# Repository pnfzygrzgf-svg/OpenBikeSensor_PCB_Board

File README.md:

# OpenBikeSensor PCB

**Hinweis:** Dieses Repository ist ein Klon/Fork des offiziellen
[OpenBikeSensor PCB-Repositories](https://github.com/openbikesensor/OpenBikeSensor_PCB_Board) und enthält zusätzliche Erweiterungen.

**Neu in diesem Fork:**
- **OpenBikeSensor Lite LiDAR** (`OpenBikeSensorLiteLidar/`) — PCB-Variante mit 2x TF-Luna LiDAR statt Ultraschallsensoren

## Versionen

### OpenBikeSensor Lite LiDAR

Im Verzeichnis `OpenBikeSensorLiteLidar` findest du die Dateien für das Modell
OpenBikeSensor Lite LiDAR (2x TF-Luna). Diese Variante basiert auf dem Lite-Konzept
(Messelektronik + Kommunikation, Programmlogik überwiegend auf dem Handy), nutzt
aber LiDAR zur Abstandsmessung.

* [Gerber (ZIP)](./OpenBikeSensorLiteLidar/plot/OpenBikeSensorLiteLidar-gerbers.zip)
* [KiCad PCB](./OpenBikeSensorLiteLidar/OpenBikeSensorLiteLidar.kicad_pcb)

### OpenBikeSensor

Dies ist der Standard-OpenBikeSensor als eigenständiges Gerät, hergestellt aus
vielen fertig verfügbaren Modulen (ESP32 Devkit, GPS, SD-Karten-Modul,
Ultraschallsensor-Module, ...).

Die aktuelle Versionsnummer des OpenBikeSensor Clasic PCB ist `1.0.0`. Den veralteten Repositorystand der Vorversion findest du [hier](https://github.com/openbikesensor/OpenBikeSensor_PCB_Board/tree/00.03.12)

* [Gerber](OpenBikeSensor1.0.0-Gerber.zip)
* [Schaltplan, PDF](./OpenBikeSensor/generated/OpenBikeSensor-1.0.0-schematic.pdf)
* [Bestückungsplan, HTML](./OpenBikeSensor/generated/OpenBikeSensor-1.0.0-ibom.html)

### OpenBikeSensor Lite

Im Verzeichnis OpenBikeSensorLite findest du die Dateien für das Modell
OpenBikeSensor Lite. Dieser OpenBikeSensor hat nur Messelektronik,
Datenspeicher, Kommunikation und ein Großteil der Programmlogik läuft
auf dem Handy in der SimRa App.

### OpenBikeSensor Pro

Diese Variante des OpenBikeSensor ist ein vollständiger Nachbau aller
relevanter Teile der vorher als Modul gelieferten Funktionen in einer eigenen
Schaltung, und ist komplett maschinenbestückt bestellbar. Dies macht das Gerät
teurer und komplizierter herstellen zu lassen, aber es ist ein wesentlich
geringerer Eigenaufwand zur Fertigstellung ohne Löten elektronischer Module
nötig. Dieses Projekt is zur Zeit in der Entwicklung und hoffentlich im Laufe
des Jahres 2023 benutzbar.

## Bestellung bei Platinenherstellern

Ein Export der Projektdateien als "Gerber-Files" liegt im jeweiligen
Projektordner vor. Die meisten Hersteller von Platinen bieten einen
Online-Konfigurator an, in den diese Dateien hochgeladen werden können, und
welcher dann auch eine Vorschau bietet. In der Regel sollten diese Exports für
alle Hersteller funktionieren, die Anforderungen an die Genauigkeit der
Produktion sind relativ gering.

Die Standardeinstellungen für die Platine sind in der Regel vollkommen
ausreichend, das ist üblicherweise ein 2-Layer Board mit einfachem Surface
Finish (HASL) in 1.6mm Stärke (FR-4) und 1oz Kupferstärke. Bessere Optionen (z.
B. ENIG) sind möglich, aber nicht nötig. Die Einstellungen können nach Belieben
angepasst werden, insbesondere ästhetische Aspekte wie die Farbe der Boards.

Einige Hersteller (z. B. Aisler) können die KiCad-Dateien direkt importieren,
hier muss nur die `.kicad_pcb` Datei ausgewählt werden, diese enthält alle
Informationen des Designs.

Bei manchen Herstellern (z. B. JLCPCB) wird die Bestellnummer auf jedes Board
aufgedruckt, für einen kleinen Mehrbetrag kann dies vermieden werden. Gerade
bei größeren Bestellungen fällt diese Gebühr kaum ins Gewicht und ist sehr zu
empfehlen.

## Lizenz

Die eigenen Inhalte dieses Repositories sind lizensiert unter den Bedingungen
der GNU Lesser General Public License. Eine Kopie der Lizenz befindet sich in der
Datei `LICENSE` in diesem Verzeichnis.

Nicht unter diese Lizenz fallen:

* Die folgenden Dateien, welche leichte Modifikationen von Standard-Footprints
  der KiCad-Bibliothek sind und somit unter der entsprechende Lizenz
  ([CC-BY-SA 4.0 mit Modifikationen](https://www.kicad.org/libraries/license/))
  stehen:
    - `libs/OpenBikeSensor.pretty/CP_Radial_D4.0mm_P1.50mm.kicad_mod`
    - `libs/OpenBikeSensor.pretty/Connector_1x02.kicad_mod`
    - `libs/OpenBikeSensor.pretty/Connector_1x04.kicad_mod`
    - `libs/OpenBikeSensor.pretty/Connector_1x05_Display.kicad_mod`
    - `libs/OpenBikeSensor.pretty/Connector_1x06.kicad_mod`

## Update der Exportdateien

Die Dateien in `generated` können mit
[KiBot](https://github.com/INTI-CMNB/KiBot) automatisch aktualisiert werden.
Eine Konfigurationsdatei liegt im jeweiligen Projektverzeichnis vor. Ein
Ausführen von `kibot` im entsprechenden Unterverzeichnis (z. B. `cd
OpenBikeSensor`) erstellt alle Exportdateien neu. Bitte checke nur solche
Dateien in git ein, welche du in deinem Commit auch inhaltlich verändert hast
(z. B. den PDF Schaltplanexport wenn der Schaltplan verändert wurde, aber nicht
wenn nur das PCB Änderungen hat).

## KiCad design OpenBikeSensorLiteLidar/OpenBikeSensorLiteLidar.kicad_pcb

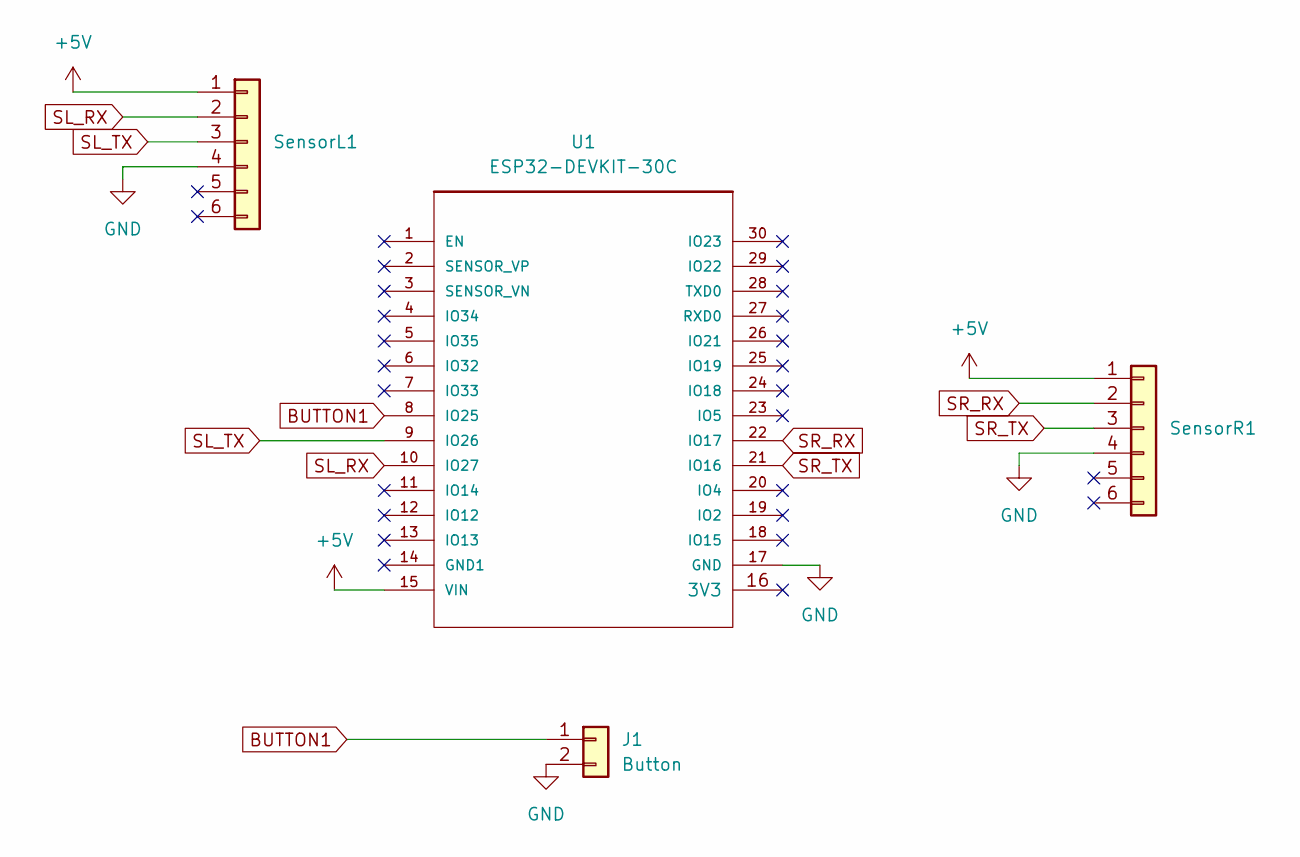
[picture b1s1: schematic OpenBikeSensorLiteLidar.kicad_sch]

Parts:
J1: Button; JST_EH_S2B-EH_1x02_P2.50mm_Horizontal
SensorL1: Conn_01x06; JST_XH_B6B-XH-A_1x06_P2.50mm_Vertical
SensorR1: Conn_01x06; JST_XH_B6B-XH-A_1x06_P2.50mm_Vertical
U1: ESP32-DEVKIT-30C; ESP32-WROOM-30-THT

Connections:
+5V: SensorL1.1, SensorR1.1, U1.15 (VIN)
BUTTON1: J1.1, U1.8 (IO25)
GND: J1.2, SensorL1.4, SensorR1.4, U1.17 (GND)
SL_RX: SensorL1.2, U1.10 (IO27)
SL_TX: SensorL1.3, U1.9 (IO26)
SR_RX: SensorR1.2, U1.22 (IO17)
SR_TX: SensorR1.3, U1.21 (IO16)

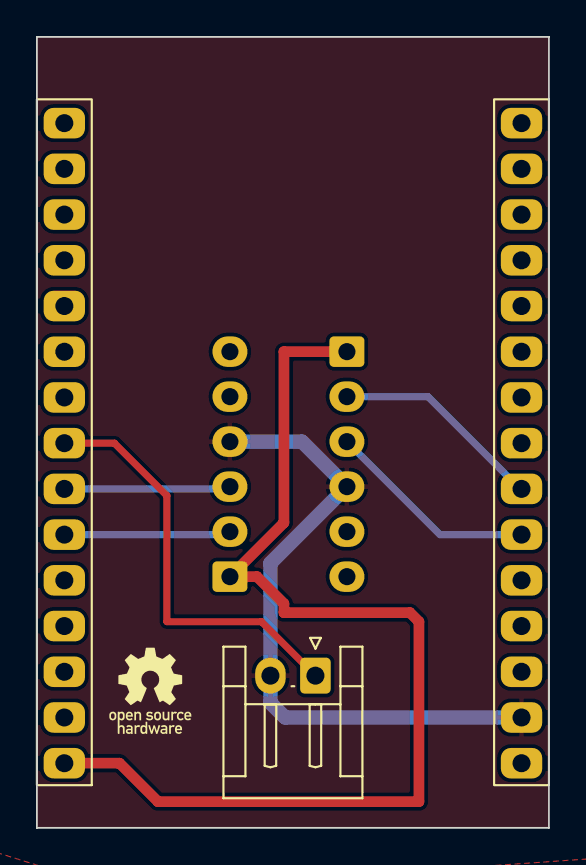
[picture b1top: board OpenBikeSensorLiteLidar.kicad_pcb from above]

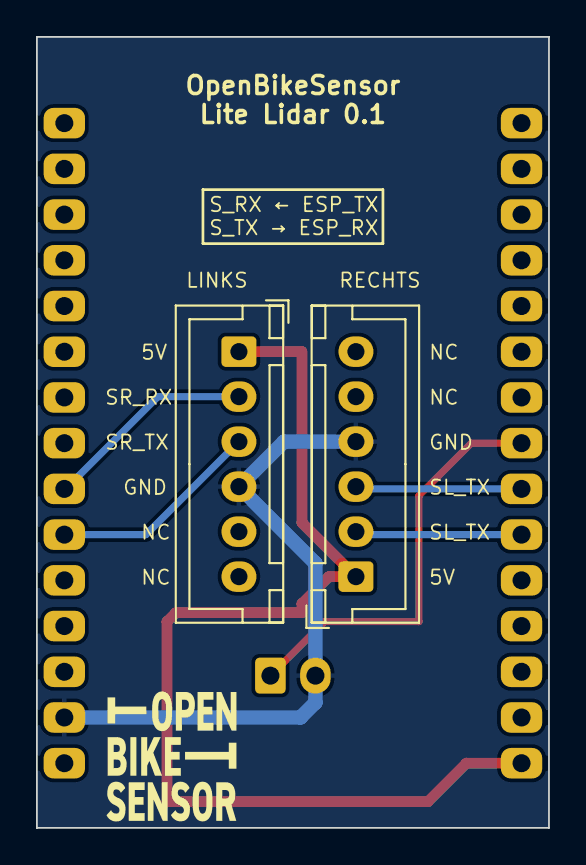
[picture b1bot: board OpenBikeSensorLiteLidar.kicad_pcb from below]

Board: 2 copper layers, 28.4 x 43.9 mm, 4 parts (2 on the bottom side), 7 nets.

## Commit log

2025-12-22 Add .gitignore for macOS files
2026-01-06 PCB für einen OpenBikeSensorLite mit Lidarsensoren
2026-01-06 Ignore KiCad lock/autosave files
2026-01-15 Swap L/R labels on Lite LiDAR PCB; update gerbers + zip
2026-02-26 Update fork notice with LiDAR PCB additions and L/R label fix
2026-02-27 Lizenz hinzugefügt
2026-03-08 Open-Source-Hardware Logo

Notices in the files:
OpenBikeSensorLiteLidar/OpenBikeSensorLiteLidar.kicad_pcb:
License: LGPL-3.0-or-later
